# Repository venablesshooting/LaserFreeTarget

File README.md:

# LaserFreeTarget
This is my initial start on making an open source 10m air laser target which would allow people to train with a low cost solution which reduces the consumables associated with electronic targets

# Maths and Assumptions
Pellet diameter: 4.5mm
Pellet length: 5.56mm
Pellet Speed: 150mm/s
Time in Beam: 37ms

37/8 = 4.625ms

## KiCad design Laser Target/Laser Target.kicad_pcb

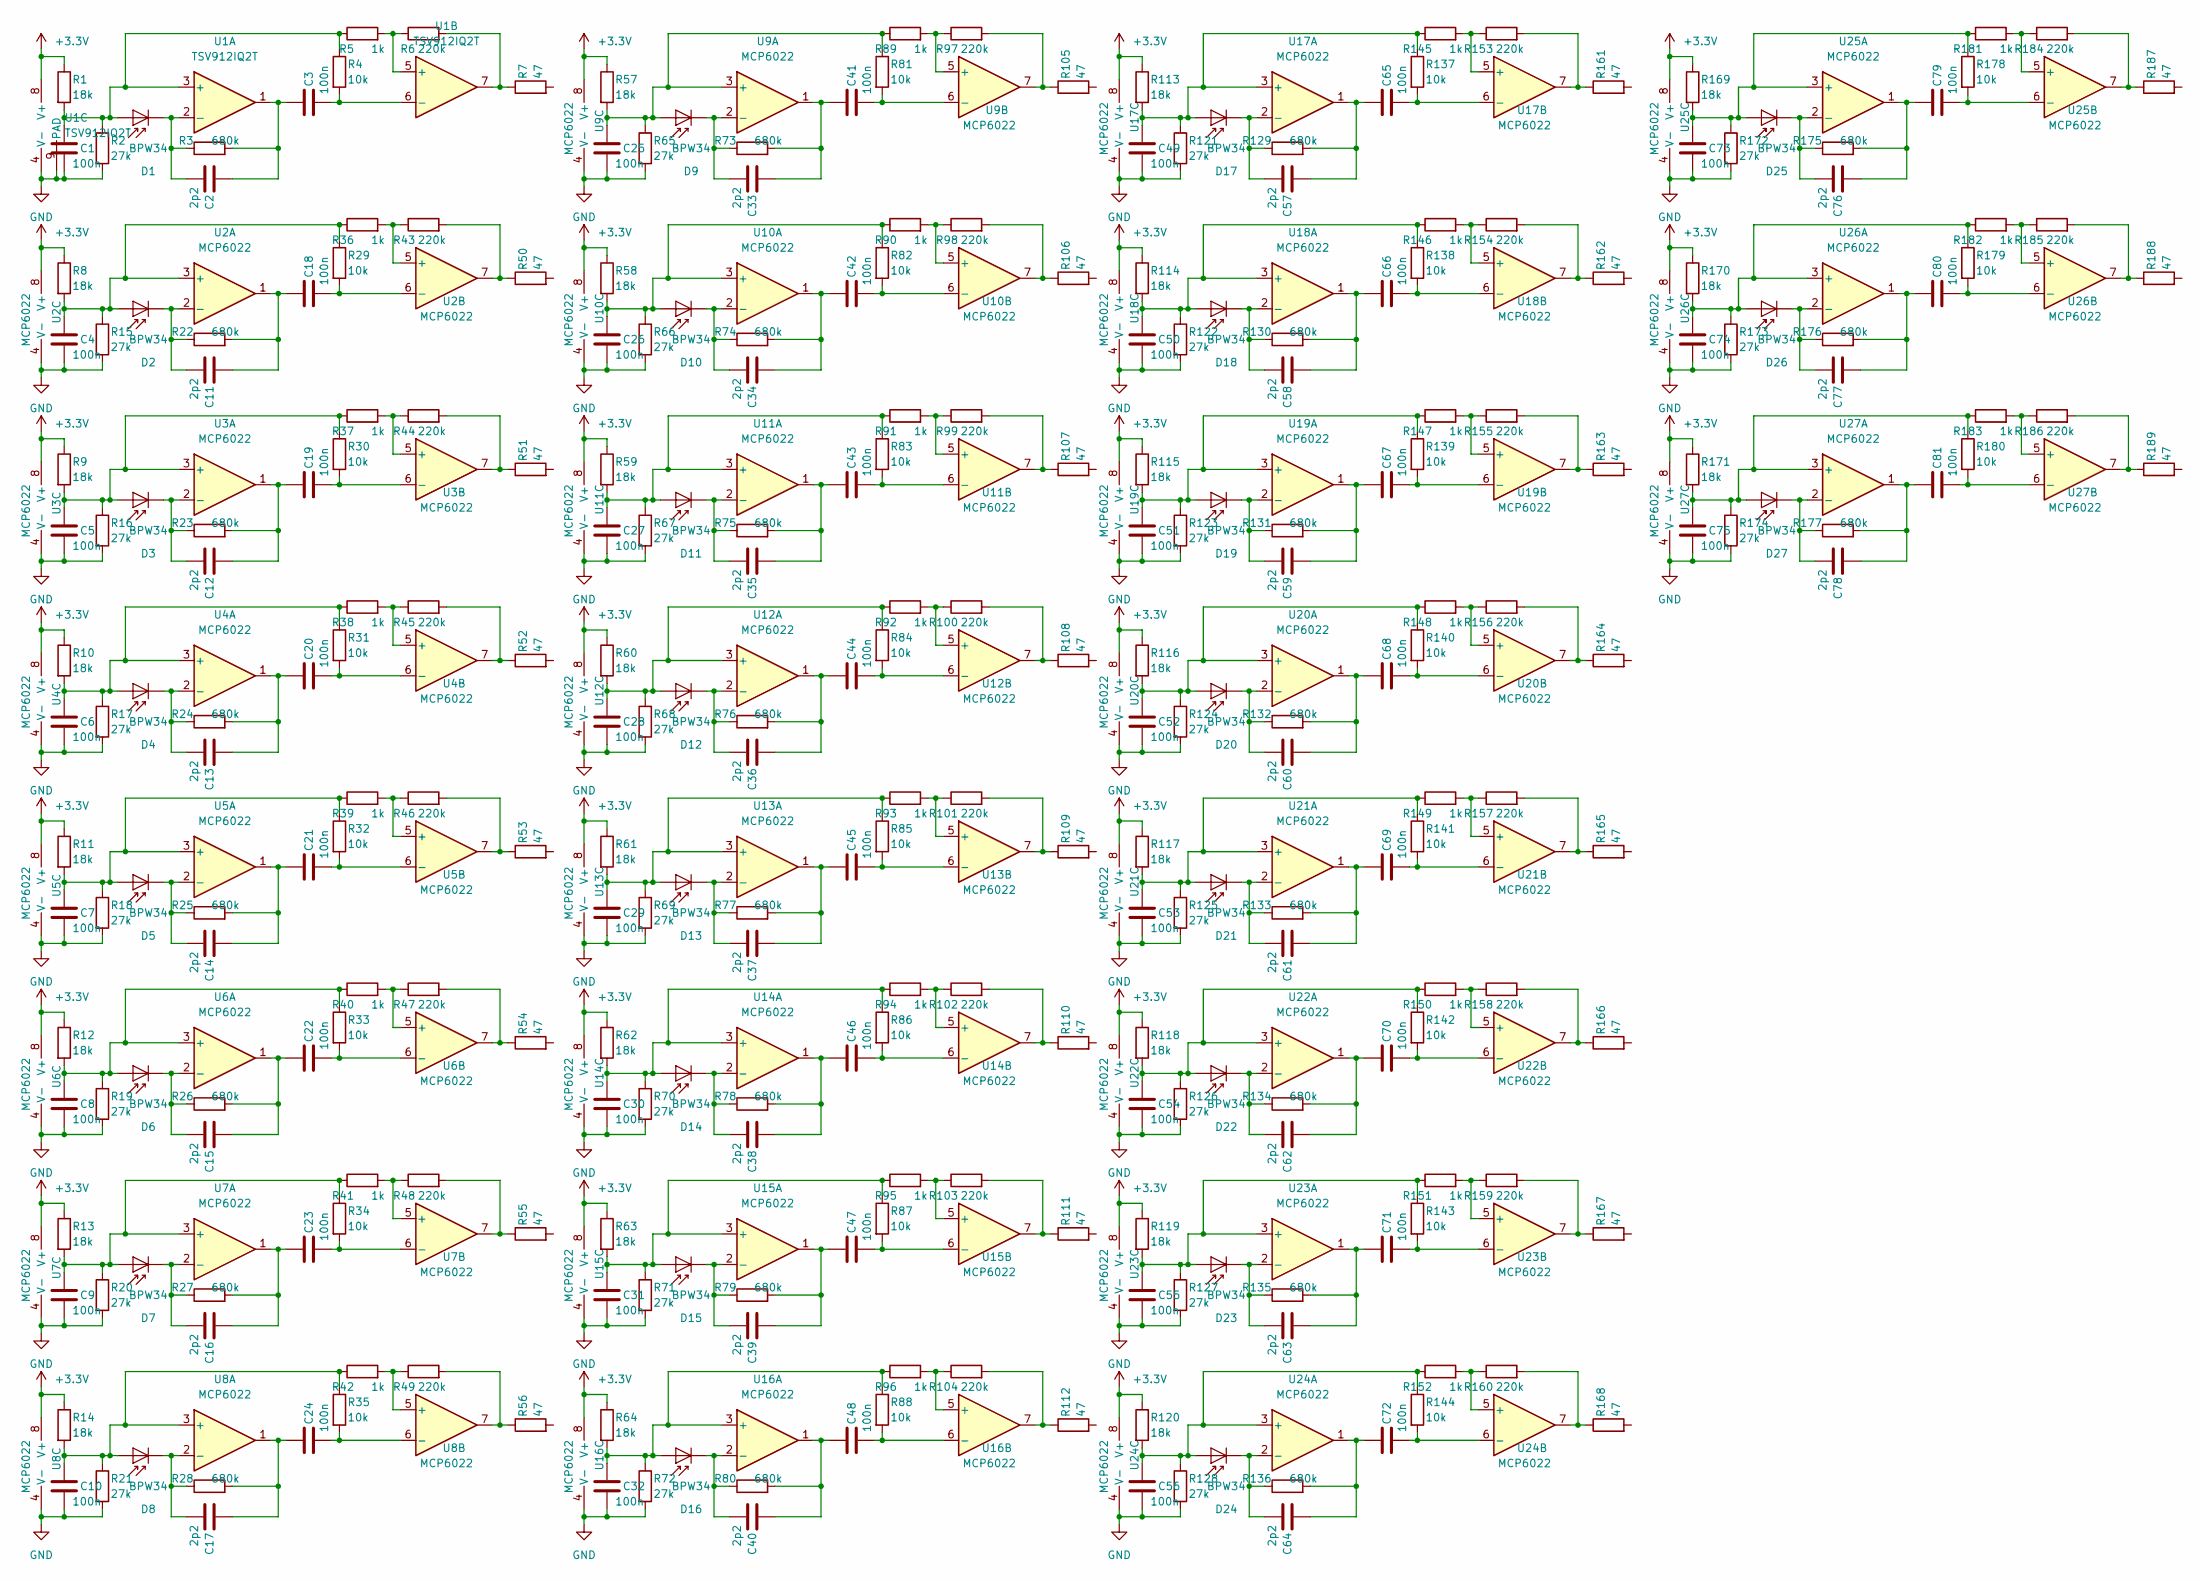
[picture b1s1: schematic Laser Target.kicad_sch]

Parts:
C1, C3, C4, C5, C6, C7, C8, C9, C10, C18, C19, C20, C21, C22, C23, C24, C25, C26, C27, C28, C29, C30, C31, C32, C41, C42, C43, C44, C45, C46, C47, C48, C49, C50, C51, C52, C53, C54, C55, C56, C65, C66, C67, C68, C69, C70, C71, C72, C73, C74, C75, C79, C80, C81: 100n; C_0603_1608Metric
C2, C11, C12, C13, C14, C15, C16, C17, C33, C34, C35, C36, C37, C38, C39, C40, C57, C58, C59, C60, C61, C62, C63, C64, C76, C77, C78: 2p2; C_0603_1608Metric
D1, D2, D3, D4, D5, D6, D7, D8, D9, D10, D11, D12, D13, D14, D15, D16, D17, D18, D19, D20, D21, D22, D23, D24, D25, D26, D27: BPW34; Osram_DIL2_4.3x4.65mm_P5.08mm
R1, R8, R9, R10, R11, R12, R13, R14, R57, R58, R59, R60, R61, R62, R63, R64, R113, R114, R115, R116, R117, R118, R119, R120, R169, R170, R171: 18k; R_0603_1608Metric
R2, R15, R16, R17, R18, R19, R20, R21, R65, R66, R67, R68, R69, R70, R71, R72, R121, R122, R123, R124, R125, R126, R127, R128, R172, R173, R174: 27k; R_0603_1608Metric
R3, R22, R23, R24, R25, R26, R27, R28, R73, R74, R75, R76, R77, R78, R79, R80, R129, R130, R131, R132, R133, R134, R135, R136, R175, R176, R177: 680k; R_0603_1608Metric
R4, R29, R30, R31, R32, R33, R34, R35, R81, R82, R83, R84, R85, R86, R87, R88, R137, R138, R139, R140, R141, R142, R143, R144, R178, R179, R180: 10k; R_0603_1608Metric
R5, R36, R37, R38, R39, R40, R41, R42, R89, R90, R91, R92, R93, R94, R95, R96, R145, R146, R147, R148, R149, R150, R151, R152, R181, R182, R183: 1k; R_0603_1608Metric
R6, R43, R44, R45, R46, R47, R48, R49, R97, R98, R99, R100, R101, R102, R103, R104, R153, R154, R155, R156, R157, R158, R159, R160, R184, R185, R186: 220k; R_0603_1608Metric
R7, R50, R51, R52, R53, R54, R55, R56, R105, R106, R107, R108, R109, R110, R111, R112, R161, R162, R163, R164, R165, R166, R167, R168, R187, R188, R189: 47; R_0603_1608Metric
U1: TSV912IQ2T; DFN-8-1EP_2x2mm_P0.5mm_EP1.05x1.75mm
U2, U3, U4, U5, U6, U7, U8, U9, U10, U11, U12, U13, U14, U15, U16, U17, U18, U19, U20, U21, U22, U23, U24, U25, U26, U27: MCP6022; SOIC-8_3.9x4.9mm_P1.27mm

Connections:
+3V3: R1.1, R8.1, R9.1, R10.1, R11.1, R12.1, R13.1, R14.1, R57.1, R58.1, R59.1, R60.1, R61.1, R62.1, R63.1, R64.1, R113.1, R114.1, R115.1, R116.1, R117.1, R118.1, R119.1, R120.1, R169.1, R170.1, R171.1, U1.8 (V+), U2.8 (V+), U3.8 (V+), U4.8 (V+), U5.8 (V+), U6.8 (V+), U7.8 (V+), U8.8 (V+), U9.8 (V+), U10.8 (V+), U11.8 (V+), U12.8 (V+), U13.8 (V+), U14.8 (V+), U15.8 (V+), U16.8 (V+), U17.8 (V+), U18.8 (V+), U19.8 (V+), U20.8 (V+), U21.8 (V+), U22.8 (V+), U23.8 (V+), U24.8 (V+), U25.8 (V+), U26.8 (V+), U27.8 (V+)
GND: C1.2, C4.2, C5.2, C6.2, C7.2, C8.2, C9.2, C10.2, C25.2, C26.2, C27.2, C28.2, C29.2, C30.2, C31.2, C32.2, C49.2, C50.2, C51.2, C52.2, C53.2, C54.2, C55.2, C56.2, C73.2, C74.2, C75.2, R2.2, R15.2, R16.2, R17.2, R18.2, R19.2, R20.2, R21.2, R65.2, R66.2, R67.2, R68.2, R69.2, R70.2, R71.2, R72.2, R121.2, R122.2, R123.2, R124.2, R125.2, R126.2, R127.2, R128.2, R172.2, R173.2, R174.2, U1.4 (V-), U1.9 (PAD), U2.4 (V-), U3.4 (V-), U4.4 (V-), U5.4 (V-), U6.4 (V-), U7.4 (V-), U8.4 (V-), U9.4 (V-), U10.4 (V-), U11.4 (V-), U12.4 (V-), U13.4 (V-), U14.4 (V-), U15.4 (V-), U16.4 (V-), U17.4 (V-), U18.4 (V-), U19.4 (V-), U20.4 (V-), U21.4 (V-), U22.4 (V-), U23.4 (V-), U24.4 (V-), U25.4 (V-), U26.4 (V-), U27.4 (V-)
unnamed: C1.1, D1.2 (A), R1.2, R2.1, R4.1, R5.1, U1.3 (+)
unnamed: C2.1, C3.1, R3.2, U1.1
unnamed: C2.2, D1.1 (K), R3.1, U1.2 (-)
unnamed: C3.2, R4.2, U1.6 (-)
unnamed: C4.1, D2.2 (A), R8.2, R15.1, R29.1, R36.1, U2.3 (+)
unnamed: C5.1, D3.2 (A), R9.2, R16.1, R30.1, R37.1, U3.3 (+)
unnamed: C6.1, D4.2 (A), R10.2, R17.1, R31.1, R38.1, U4.3 (+)
unnamed: C7.1, D5.2 (A), R11.2, R18.1, R32.1, R39.1, U5.3 (+)
unnamed: C8.1, D6.2 (A), R12.2, R19.1, R33.1, R40.1, U6.3 (+)
unnamed: C9.1, D7.2 (A), R13.2, R20.1, R34.1, R41.1, U7.3 (+)
unnamed: C10.1, D8.2 (A), R14.2, R21.1, R35.1, R42.1, U8.3 (+)
unnamed: C11.1, C18.1, R22.2, U2.1
unnamed: C11.2, D2.1 (K), R22.1, U2.2 (-)
unnamed: C12.1, C19.1, R23.2, U3.1
unnamed: C12.2, D3.1 (K), R23.1, U3.2 (-)
unnamed: C13.1, C20.1, R24.2, U4.1
unnamed: C13.2, D4.1 (K), R24.1, U4.2 (-)
unnamed: C14.1, C21.1, R25.2, U5.1
unnamed: C14.2, D5.1 (K), R25.1, U5.2 (-)
unnamed: C15.1, C22.1, R26.2, U6.1
unnamed: C15.2, D6.1 (K), R26.1, U6.2 (-)
unnamed: C16.1, C23.1, R27.2, U7.1
unnamed: C16.2, D7.1 (K), R27.1, U7.2 (-)
unnamed: C17.1, C24.1, R28.2, U8.1
unnamed: C17.2, D8.1 (K), R28.1, U8.2 (-)
unnamed: C18.2, R29.2, U2.6 (-)
unnamed: C19.2, R30.2, U3.6 (-)
unnamed: C20.2, R31.2, U4.6 (-)
unnamed: C21.2, R32.2, U5.6 (-)
unnamed: C22.2, R33.2, U6.6 (-)
unnamed: C23.2, R34.2, U7.6 (-)
unnamed: C24.2, R35.2, U8.6 (-)
unnamed: C25.1, D9.2 (A), R57.2, R65.1, R81.1, R89.1, U9.3 (+)
unnamed: C26.1, D10.2 (A), R58.2, R66.1, R82.1, R90.1, U10.3 (+)
unnamed: C27.1, D11.2 (A), R59.2, R67.1, R83.1, R91.1, U11.3 (+)
unnamed: C28.1, D12.2 (A), R60.2, R68.1, R84.1, R92.1, U12.3 (+)
unnamed: C29.1, D13.2 (A), R61.2, R69.1, R85.1, R93.1, U13.3 (+)
unnamed: C30.1, D14.2 (A), R62.2, R70.1, R86.1, R94.1, U14.3 (+)
unnamed: C31.1, D15.2 (A), R63.2, R71.1, R87.1, R95.1, U15.3 (+)
unnamed: C32.1, D16.2 (A), R64.2, R72.1, R88.1, R96.1, U16.3 (+)
unnamed: C33.1, C41.1, R73.2, U9.1
unnamed: C33.2, D9.1 (K), R73.1, U9.2 (-)
unnamed: C34.1, C42.1, R74.2, U10.1
unnamed: C34.2, D10.1 (K), R74.1, U10.2 (-)
unnamed: C35.1, C43.1, R75.2, U11.1
unnamed: C35.2, D11.1 (K), R75.1, U11.2 (-)
unnamed: C36.1, C44.1, R76.2, U12.1
unnamed: C36.2, D12.1 (K), R76.1, U12.2 (-)
unnamed: C37.1, C45.1, R77.2, U13.1
unnamed: C37.2, D13.1 (K), R77.1, U13.2 (-)
unnamed: C38.1, C46.1, R78.2, U14.1
unnamed: C38.2, D14.1 (K), R78.1, U14.2 (-)
unnamed: C39.1, C47.1, R79.2, U15.1
unnamed: C39.2, D15.1 (K), R79.1, U15.2 (-)
unnamed: C40.1, C48.1, R80.2, U16.1
unnamed: C40.2, D16.1 (K), R80.1, U16.2 (-)
unnamed: C41.2, R81.2, U9.6 (-)
unnamed: C42.2, R82.2, U10.6 (-)
unnamed: C43.2, R83.2, U11.6 (-)
unnamed: C44.2, R84.2, U12.6 (-)
unnamed: C45.2, R85.2, U13.6 (-)
unnamed: C46.2, R86.2, U14.6 (-)
unnamed: C47.2, R87.2, U15.6 (-)
unnamed: C48.2, R88.2, U16.6 (-)
unnamed: C49.1, D17.2 (A), R113.2, R121.1, R137.1, R145.1, U17.3 (+)
unnamed: C50.1, D18.2 (A), R114.2, R122.1, R138.1, R146.1, U18.3 (+)
unnamed: C51.1, D19.2 (A), R115.2, R123.1, R139.1, R147.1, U19.3 (+)
unnamed: C52.1, D20.2 (A), R116.2, R124.1, R140.1, R148.1, U20.3 (+)
unnamed: C53.1, D21.2 (A), R117.2, R125.1, R141.1, R149.1, U21.3 (+)
unnamed: C54.1, D22.2 (A), R118.2, R126.1, R142.1, R150.1, U22.3 (+)
unnamed: C55.1, D23.2 (A), R119.2, R127.1, R143.1, R151.1, U23.3 (+)
unnamed: C56.1, D24.2 (A), R120.2, R128.1, R144.1, R152.1, U24.3 (+)
unnamed: C57.1, C65.1, R129.2, U17.1
unnamed: C57.2, D17.1 (K), R129.1, U17.2 (-)
unnamed: C58.1, C66.1, R130.2, U18.1
unnamed: C58.2, D18.1 (K), R130.1, U18.2 (-)
unnamed: C59.1, C67.1, R131.2, U19.1
unnamed: C59.2, D19.1 (K), R131.1, U19.2 (-)
unnamed: C60.1, C68.1, R132.2, U20.1
unnamed: C60.2, D20.1 (K), R132.1, U20.2 (-)
unnamed: C61.1, C69.1, R133.2, U21.1
unnamed: C61.2, D21.1 (K), R133.1, U21.2 (-)
unnamed: C62.1, C70.1, R134.2, U22.1
unnamed: C62.2, D22.1 (K), R134.1, U22.2 (-)
unnamed: C63.1, C71.1, R135.2, U23.1
unnamed: C63.2, D23.1 (K), R135.1, U23.2 (-)
unnamed: C64.1, C72.1, R136.2, U24.1
unnamed: C64.2, D24.1 (K), R136.1, U24.2 (-)
unnamed: C65.2, R137.2, U17.6 (-)
unnamed: C66.2, R138.2, U18.6 (-)
unnamed: C67.2, R139.2, U19.6 (-)
unnamed: C68.2, R140.2, U20.6 (-)
unnamed: C69.2, R141.2, U21.6 (-)
unnamed: C70.2, R142.2, U22.6 (-)
unnamed: C71.2, R143.2, U23.6 (-)
unnamed: C72.2, R144.2, U24.6 (-)
unnamed: C73.1, D25.2 (A), R169.2, R172.1, R178.1, R181.1, U25.3 (+)
unnamed: C74.1, D26.2 (A), R170.2, R173.1, R179.1, R182.1, U26.3 (+)
unnamed: C75.1, D27.2 (A), R171.2, R174.1, R180.1, R183.1, U27.3 (+)
unnamed: C76.1, C79.1, R175.2, U25.1
unnamed: C76.2, D25.1 (K), R175.1, U25.2 (-)
unnamed: C77.1, C80.1, R176.2, U26.1
unnamed: C77.2, D26.1 (K), R176.1, U26.2 (-)
unnamed: C78.1, C81.1, R177.2, U27.1
unnamed: C78.2, D27.1 (K), R177.1, U27.2 (-)
unnamed: C79.2, R178.2, U25.6 (-)
unnamed: C80.2, R179.2, U26.6 (-)
unnamed: C81.2, R180.2, U27.6 (-)
unnamed: R5.2, R6.1, U1.5 (+)
unnamed: R6.2, R7.1, U1.7
unnamed: R36.2, R43.1, U2.5 (+)
unnamed: R37.2, R44.1, U3.5 (+)
unnamed: R38.2, R45.1, U4.5 (+)
unnamed: R39.2, R46.1, U5.5 (+)
unnamed: R40.2, R47.1, U6.5 (+)
unnamed: R41.2, R48.1, U7.5 (+)
unnamed: R42.2, R49.1, U8.5 (+)
unnamed: R43.2, R50.1, U2.7
unnamed: R44.2, R51.1, U3.7
unnamed: R45.2, R52.1, U4.7
unnamed: R46.2, R53.1, U5.7
unnamed: R47.2, R54.1, U6.7
unnamed: R48.2, R55.1, U7.7
unnamed: R49.2, R56.1, U8.7
unnamed: R89.2, R97.1, U9.5 (+)
unnamed: R90.2, R98.1, U10.5 (+)
unnamed: R91.2, R99.1, U11.5 (+)
unnamed: R92.2, R100.1, U12.5 (+)
unnamed: R100.2, R108.1, U12.7
unnamed: R93.2, R101.1, U13.5 (+)
unnamed: R101.2, R109.1, U13.7
unnamed: R94.2, R102.1, U14.5 (+)
unnamed: R102.2, R110.1, U14.7
unnamed: R95.2, R103.1, U15.5 (+)
unnamed: R103.2, R111.1, U15.7
unnamed: R96.2, R104.1, U16.5 (+)
unnamed: R104.2, R112.1, U16.7
unnamed: R97.2, R105.1, U9.7
unnamed: R98.2, R106.1, U10.7
unnamed: R99.2, R107.1, U11.7
unnamed: R145.2, R153.1, U17.5 (+)
unnamed: R146.2, R154.1, U18.5 (+)
unnamed: R147.2, R155.1, U19.5 (+)
unnamed: R148.2, R156.1, U20.5 (+)
unnamed: R149.2, R157.1, U21.5 (+)
unnamed: R150.2, R158.1, U22.5 (+)
unnamed: R151.2, R159.1, U23.5 (+)
unnamed: R152.2, R160.1, U24.5 (+)
unnamed: R153.2, R161.1, U17.7
unnamed: R154.2, R162.1, U18.7
unnamed: R155.2, R163.1, U19.7
unnamed: R156.2, R164.1, U20.7
unnamed: R157.2, R165.1, U21.7
unnamed: R158.2, R166.1, U22.7
unnamed: R159.2, R167.1, U23.7
unnamed: R160.2, R168.1, U24.7
unnamed: R181.2, R184.1, U25.5 (+)
unnamed: R182.2, R185.1, U26.5 (+)
unnamed: R183.2, R186.1, U27.5 (+)
unnamed: R184.2, R187.1, U25.7
unnamed: R185.2, R188.1, U26.7
unnamed: R186.2, R189.1, U27.7

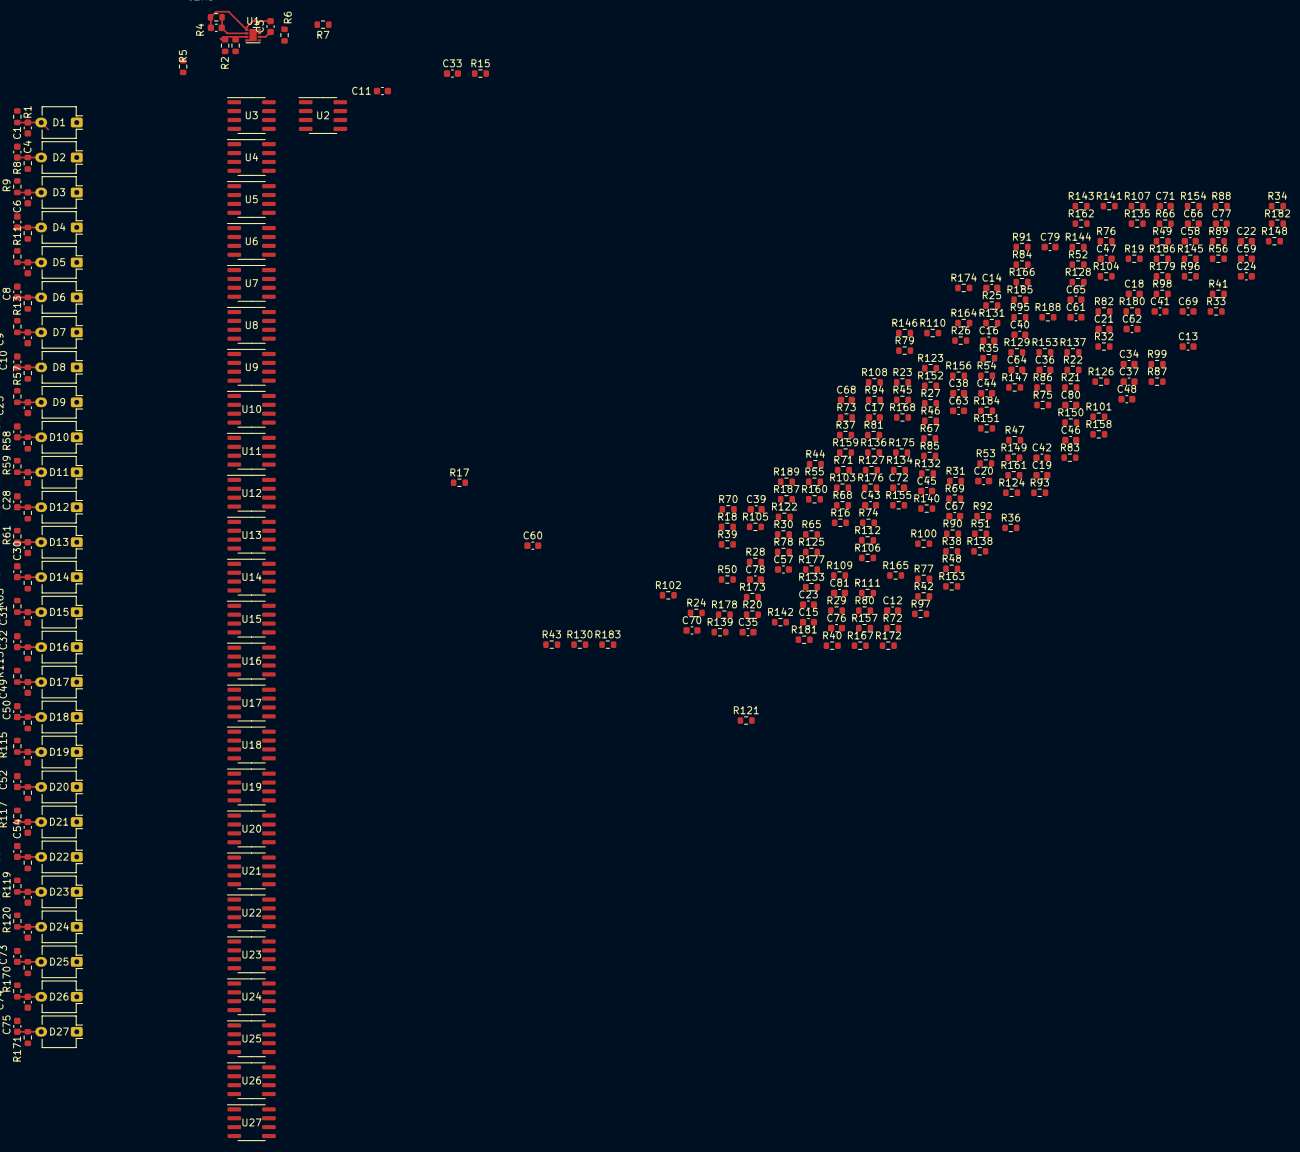
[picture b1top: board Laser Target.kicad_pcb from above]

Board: 2 copper layers, 324 parts (0 on the bottom side), 164 nets.
